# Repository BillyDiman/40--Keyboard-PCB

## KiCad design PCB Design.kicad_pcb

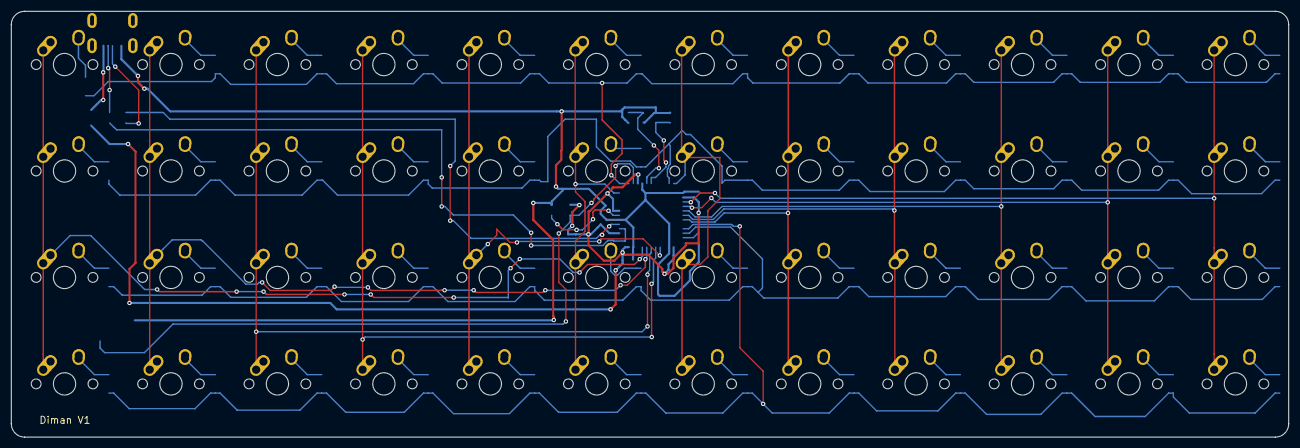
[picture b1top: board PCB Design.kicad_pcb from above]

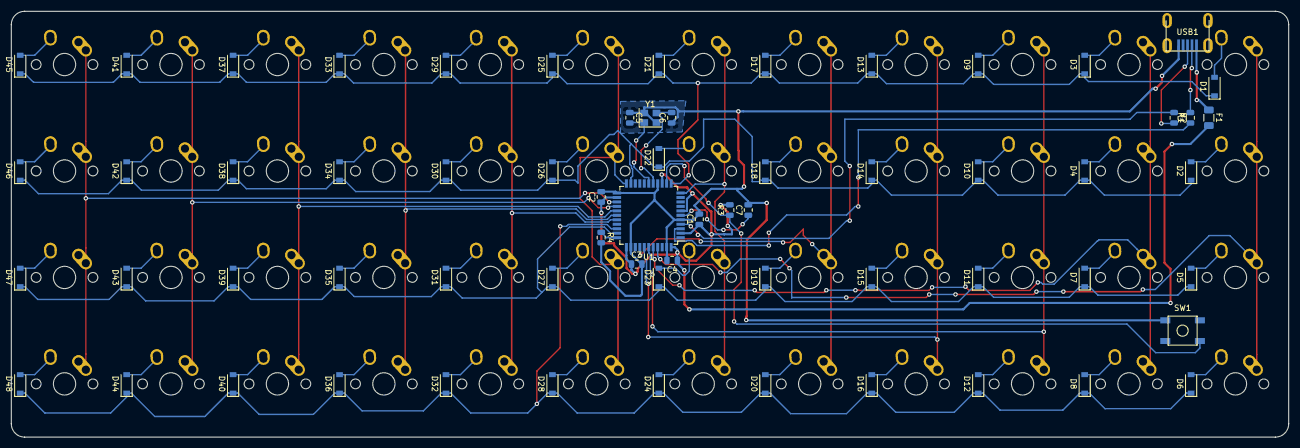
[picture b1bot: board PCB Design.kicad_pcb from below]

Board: 2 copper layers, 228.6 x 76.2 mm, 112 parts (64 on the bottom side), 76 nets.

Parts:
C1, C2, C3: 0.1uF; C_0805_2012Metric
C4: 10uF; C_0805_2012Metric
C5, C6: 22pF; C_0805_2012Metric
C7: 1uF; C_0805_2012Metric
D1, D2, D3, D4, D5, D6, D7, D8, D9, D10, D11, D12, D13, D14, D15, D16, D17, D18, D19, D20, D21, D22, D23, D24, D25, D26, D27, D28, D29, D30, D31, D32, D33, D34, D35, D36, D37, D38, D39, D40, D41, D42, D43, D44, D45, D46, D47, D48: D_Small; D_SOD-123
F1: 500mA; Fuse_1206_3216Metric
MX1, MX2, MX3, MX4, MX5, MX6, MX7, MX8, MX9, MX10, MX11, MX12, MX13, MX14, MX15, MX16, MX17, MX18, MX19, MX20, MX21, MX22, MX23, MX24, MX25, MX26, MX27, MX28, MX29, MX30, MX31, MX32, MX33, MX34, MX35, MX36, MX37, MX38, MX39, MX40, MX41, MX42, MX43, MX44, MX45, MX46, MX47, MX48: MX-NoLED; MX-1U-NoLED
R1, R2: 22; R_0805_2012Metric
R3, R4: 10k; R_0805_2012Metric
SW1: SW_Push; SKQG-1155865
U1: ATmega32U4-AU; TQFP-44_10x10mm_P0.8mm
USB1: Molex-0548190589
Y1: 16MHz; Crystal_SMD_3225-4Pin_3.2x2.5mm

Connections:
+5V: C1.1, C2.1, C3.1, C4.1, F1.2, R3.2, U1.2, U1.7, U1.14, U1.24, U1.34, U1.44
D+: R2.2, USB1.3
D-: R1.2, USB1.4
GND: C1.2, C2.2, C3.2, C4.2, C5.1, C6.1, C7.2, R4.2, SW1.1, U1.5, U1.15, U1.23, U1.35, U1.43, USB1.1, USB1.6, Y1.2, Y1.4
unnamed: C5.2, U1.17, Y1.1
unnamed: C6.2, U1.16, Y1.3
unnamed: C7.1, U1.6
unnamed: D1.2, MX1.2
unnamed: D2.2, MX2.2
unnamed: D3.2, MX3.2
unnamed: D4.2, MX4.2
unnamed: D5.2, MX5.2
unnamed: D6.2, MX6.2
unnamed: D7.2, MX7.2
unnamed: D8.2, MX8.2
unnamed: D9.2, MX9.2
unnamed: D10.2, MX10.2
unnamed: D11.2, MX11.2
unnamed: D12.2, MX12.2
unnamed: D13.2, MX13.2
unnamed: D14.2, MX14.2
unnamed: D15.2, MX15.2
unnamed: D16.2, MX16.2
unnamed: D17.2, MX17.2
unnamed: D18.2, MX18.2
unnamed: D19.2, MX19.2
unnamed: D20.2, MX20.2
unnamed: D21.2, MX21.2
unnamed: D22.2, MX22.2
unnamed: D23.2, MX23.2
unnamed: D24.2, MX24.2
unnamed: D25.2, MX25.2
unnamed: D26.2, MX26.2
unnamed: D27.2, MX27.2
unnamed: D28.2, MX28.2
unnamed: D29.2, MX29.2
unnamed: D30.2, MX30.2
unnamed: D31.2, MX31.2
unnamed: D32.2, MX32.2
unnamed: D33.2, MX33.2
unnamed: D34.2, MX34.2
unnamed: D35.2, MX35.2
unnamed: D36.2, MX36.2
unnamed: D37.2, MX37.2
unnamed: D38.2, MX38.2
unnamed: D39.2, MX39.2
unnamed: D40.2, MX40.2
unnamed: D41.2, MX41.2
unnamed: D42.2, MX42.2
unnamed: D43.2, MX43.2
unnamed: D44.2, MX44.2
unnamed: D45.2, MX45.2
unnamed: D46.2, MX46.2
unnamed: D47.2, MX47.2
unnamed: D48.2, MX48.2
unnamed: R1.1, U1.3
unnamed: R2.1, U1.4
unnamed: R3.1, SW1.2, U1.13
unnamed: R4.1, U1.33
VCC: F1.1, USB1.5
col0: MX1.1, MX2.1, MX5.1, MX6.1, U1.41
col1: MX3.1, MX4.1, MX7.1, MX8.1, U1.40
col2: MX9.1, MX10.1, MX11.1, MX12.1, U1.39
col3: MX13.1, MX14.1, MX15.1, MX16.1, U1.38
col4: MX17.1, MX18.1, MX19.1, MX20.1, U1.37
col5: MX21.1, MX22.1, MX23.1, MX24.1, U1.11
col6: MX25.1, MX26.1, MX27.1, MX28.1, U1.22
col7: MX29.1, MX30.1, MX31.1, MX32.1, U1.29
col8: MX33.1, MX34.1, MX35.1, MX36.1, U1.28
col9: MX37.1, MX38.1, MX39.1, MX40.1, U1.27
col10: MX41.1, MX42.1, MX43.1, MX44.1, U1.26
col11: MX45.1, MX46.1, MX47.1, MX48.1, U1.25
row0: D1.1, D3.1, D9.1, D13.1, D17.1, D21.1, D25.1, D29.1, D33.1, D37.1, D41.1, D45.1, U1.12
row1: D2.1, D4.1, D10.1, D14.1, D18.1, D22.1, D26.1, D30.1, D34.1, D38.1, D42.1, D46.1, U1.21
row2: D5.1, D7.1, D11.1, D15.1, D19.1, D23.1, D27.1, D31.1, D35.1, D39.1, D43.1, D47.1, U1.32
row3: D6.1, D8.1, D12.1, D16.1, D20.1, D24.1, D28.1, D32.1, D36.1, D40.1, D44.1, D48.1, U1.31

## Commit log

2024-11-04 Creating Project
2024-11-04 Added kicad modules
2024-11-04 Configuring kicad modules for project
2024-11-04 Mcu zone completed
2024-11-04 Main schematic finished
2024-11-04 Assigning library components to schematic, need to figure out mx_alps_hybrid library issue
2024-11-04 Figured out mx lib issue
2024-11-04 Beginning pcb
2024-11-04 Preliminary PCB layout for 4 switch board
2024-11-04 Editing schematic to include all 48 keys
2024-11-04 Diode layout completed
2024-11-04 Pre-trace, need to figure out how to place microcontroller on board itself
2024-11-05 Preliminary PCB completed
2024-11-05 Done with switch traces
2024-11-05 Working on trace pt.1
2024-11-05 Finished routing
2024-11-05 Figuring out routing and ground fill
